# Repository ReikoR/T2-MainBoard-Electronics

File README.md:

T2-MainBoard-Electronics
========================

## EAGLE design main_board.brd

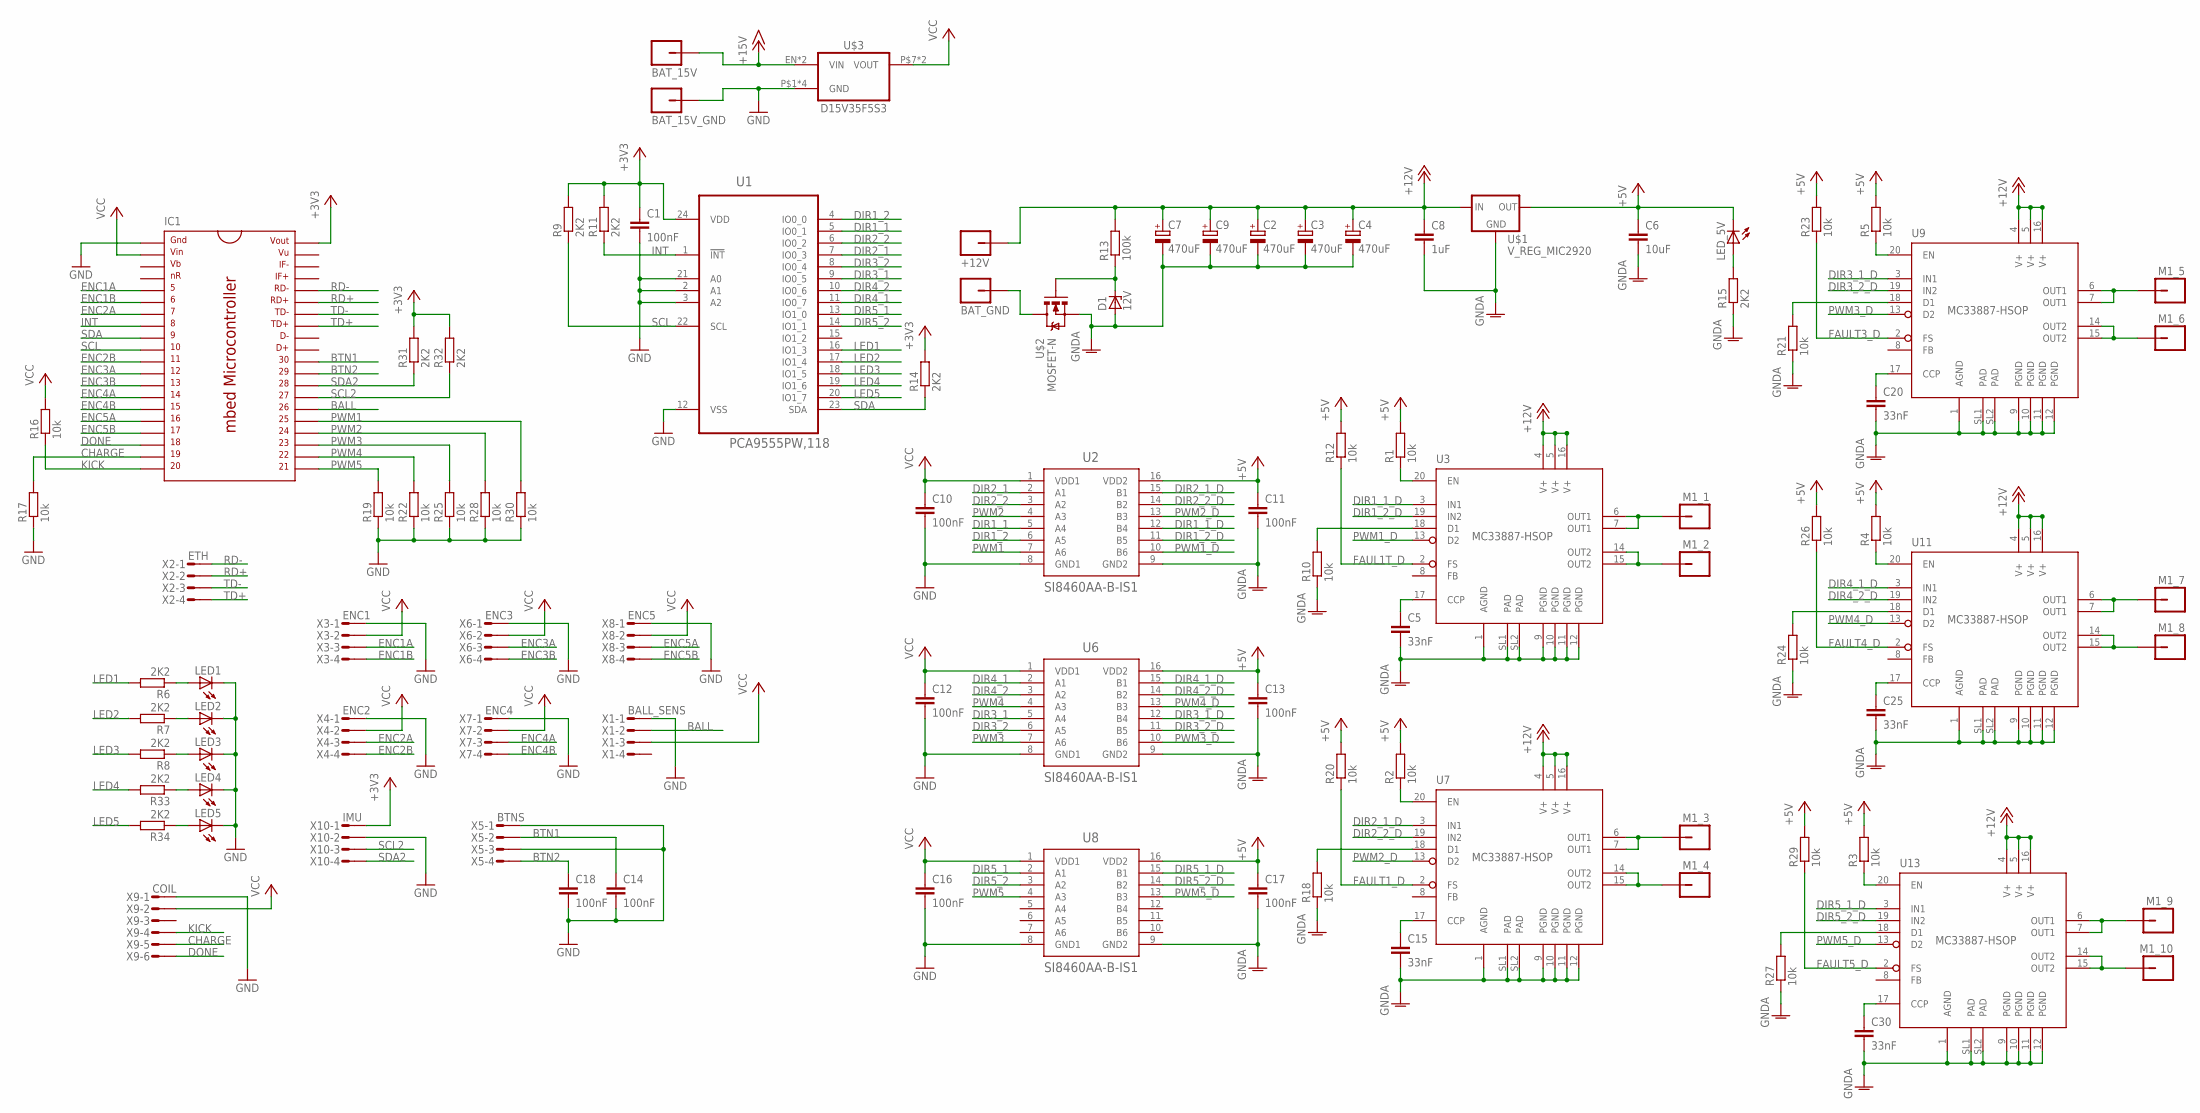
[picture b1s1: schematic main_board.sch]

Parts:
+12V: M01_PWR; PWR_HOLE
BAT_15V, BAT_15V_GND: M01_WIRE; WIRE_HOLE
BAT_GND: M01_PWR; PWR_HOLE
C1, C10, C11, C12, C13, C14, C16, C17, C18: 100nF; C0603K
C2, C3, C4, C7, C9: 470uF; E3,5-8
C5, C15, C20, C25, C30: 33nF; C0603K
C6: 10uF; C1206K
C8: 1uF; C0603K
D1: 12V; SOD123
IC1: MBED_MICROCONTROLLER; DIL40_0.9
LED1, LED2, LED3, LED4, LED5: LEDCHIP-LED0603; CHIP-LED0603
LED_5V: LEDCHIP-LED0603; CHIP-LED0603
M1_1, M1_2, M1_3, M1_4, M1_5, M1_6, M1_7, M1_8, M1_9, M1_10: M01_WIRE; WIRE_HOLE
R1, R2, R3, R4, R5, R10, R12, R16, R17, R18, R19, R20, R21, R22, R23, R24, R25, R26, R27, R28, R29, R30: 10k; R0603
R6, R7, R8, R9, R11, R14, R15, R31, R32, R33, R34: 2K2; R0603
R13: 100k; R0603
U1: PCA9555PW,118; SOP65P640X110-24N
U2, U6, U8: SI8460AA-B-IS1; SOIC-16
U3, U7, U9, U11, U13: MC33887-HSOP; HSOP
U$1: V_REG_MIC2920; SOT223
U$2: MOSFET-N; TO127P600X120-5N
U$3: D15V35F5S3
X1: BALL_SENS; MICROMATCH-4
X2: ETH; MICROMATCH-4
X3: ENC1; MICROMATCH-4
X4: ENC2; MICROMATCH-4
X5: BTNS; MICROMATCH-4
X6: ENC3; MICROMATCH-4
X7: ENC4; MICROMATCH-4
X8: ENC5; MICROMATCH-4
X9: COIL; MICROMATCH-6
X10: IMU; MICROMATCH-4

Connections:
+3V3: C1.1, IC1.40, R9.2, R11.2, R14.2, R31.2, R32.2, U1.24 (VDD), X10.1
+5V: C6.1, C11.1, C13.1, C17.1, LED_5V.C, R1.2, R2.2, R3.2, R4.2, R5.2, R12.2, R20.2, R23.2, R26.2, R29.2, U2.16 (VDD2), U6.16 (VDD2), U8.16 (VDD2), U$1.3 (OUT)
+12V: +12V.P$1, C2.+, C3.+, C4.+, C7.+, C8.1, C9.+, R13.2, U3.4 (V+), U3.5 (V+), U3.16 (V+), U7.4 (V+), U7.5 (V+), U7.16 (V+), U9.4 (V+), U9.5 (V+), U9.16 (V+), U11.4 (V+), U11.5 (V+), U11.16 (V+), U13.4 (V+), U13.5 (V+), U13.16 (V+), U$1.1 (IN)
+15V: BAT_15V.P$1, U$3.EN (VIN), U$3.P$5 (VIN)
BALL: IC1.26, X1.2
BTN1: C14.1, IC1.30, X5.2
BTN2: C18.1, IC1.29, X5.4
CHARGE: IC1.19, R17.2, X9.5
DIR1_1: U1.5 (IO0_1), U2.5 (A4)
DIR1_1_D: U2.12 (B4), U3.3 (IN1)
DIR1_2: U1.4 (IO0_0), U2.6 (A5)
DIR1_2_D: U2.11 (B5), U3.19 (IN2)
DIR2_1: U1.7 (IO0_3), U2.2 (A1)
DIR2_1_D: U2.15 (B1), U7.3 (IN1)
DIR2_2: U1.6 (IO0_2), U2.3 (A2)
DIR2_2_D: U2.14 (B2), U7.19 (IN2)
DIR3_1: U1.9 (IO0_5), U6.5 (A4)
DIR3_1_D: U6.12 (B4), U9.3 (IN1)
DIR3_2: U1.8 (IO0_4), U6.6 (A5)
DIR3_2_D: U6.11 (B5), U9.19 (IN2)
DIR4_1: U1.11 (IO0_7), U6.2 (A1)
DIR4_1_D: U6.15 (B1), U11.3 (IN1)
DIR4_2: U1.10 (IO0_6), U6.3 (A2)
DIR4_2_D: U6.14 (B2), U11.19 (IN2)
DIR5_1: U1.13 (IO1_0), U8.2 (A1)
DIR5_1_D: U8.15 (B1), U13.3 (IN1)
DIR5_2: U1.14 (IO1_1), U8.3 (A2)
DIR5_2_D: U8.14 (B2), U13.19 (IN2)
DONE: IC1.18, X9.6
ENC1A: IC1.5, X3.3
ENC1B: IC1.6, X3.4
ENC2A: IC1.7, X4.3
ENC2B: IC1.11, X4.4
ENC3A: IC1.12, X6.3
ENC3B: IC1.13, X6.4
ENC4A: IC1.14, X7.3
ENC4B: IC1.15, X7.4
ENC5A: IC1.16, X8.3
ENC5B: IC1.17, X8.4
FAUL1T_D: R12.1, U3.2 (FS)
FAULT1_D: R20.1, U7.2 (FS)
FAULT3_D: R23.1, U9.2 (FS)
FAULT4_D: R26.1, U11.2 (FS)
FAULT5_D: R29.1, U13.2 (FS)
GND: BAT_15V_GND.P$1, C1.2, C10.2, C12.2, C14.2, C16.2, C18.2, IC1.1, LED1.C, LED2.C, LED3.C, LED4.C, LED5.C, R17.1, R19.1, R22.1, R25.1, R28.1, R30.1, U1.2 (A1), U1.3 (A2), U1.12 (VSS), U1.21 (A0), U2.8 (GND1), U6.8 (GND1), U8.8 (GND1), U$3.P$1 (GND), U$3.P$2 (GND), U$3.P$3 (GND), U$3.P$4 (GND), X1.1, X3.1, X4.1, X5.1, X5.3, X6.1, X7.1, X8.1, X9.1, X10.2
GNDA: C2.-, C3.-, C4.-, C5.2, C6.2, C7.-, C8.2, C9.-, C11.2, C13.2, C15.2, C17.2, C20.2, C25.2, C30.2, D1.A, R10.1, R15.1, R18.1, R21.1, R24.1, R27.1, U2.9 (GND2), U3.1 (AGND), U3.9 (PGND), U3.10 (PGND), U3.11 (PGND), U3.12 (PGND), U3.SL1 (PAD), U3.SL2 (PAD), U6.9 (GND2), U7.1 (AGND), U7.9 (PGND), U7.10 (PGND), U7.11 (PGND), U7.12 (PGND), U7.SL1 (PAD), U7.SL2 (PAD), U8.9 (GND2), U9.1 (AGND), U9.9 (PGND), U9.10 (PGND), U9.11 (PGND), U9.12 (PGND), U9.SL1 (PAD), U9.SL2 (PAD), U11.1 (AGND), U11.9 (PGND), U11.10 (PGND), U11.11 (PGND), U11.12 (PGND), U11.SL1 (PAD), U11.SL2 (PAD), U13.1 (AGND), U13.9 (PGND), U13.10 (PGND), U13.11 (PGND), U13.12 (PGND), U13.SL1 (PAD), U13.SL2 (PAD), U$1.2 (GND), U$1.4 (GND), U$2.1 (S), U$2.2 (S), U$2.3 (S)
INT: IC1.8, R11.1, U1.1 (!INT)
KICK: IC1.20, R16.1, X9.4
LED1: R6.2, U1.16 (IO1_3)
LED2: R7.2, U1.17 (IO1_4)
LED3: R8.2, U1.18 (IO1_5)
LED4: R33.2, U1.19 (IO1_6)
LED5: R34.2, U1.20 (IO1_7)
unnamed: R1.1, U3.20 (EN)
unnamed: R2.1, U7.20 (EN)
unnamed: R3.1, U13.20 (EN)
unnamed: R4.1, U11.20 (EN)
unnamed: R5.1, U9.20 (EN)
unnamed: LED1.A, R6.1
unnamed: LED2.A, R7.1
unnamed: LED3.A, R8.1
unnamed: LED_5V.A, R15.2
unnamed: LED4.A, R33.1
unnamed: LED5.A, R34.1
unnamed: C5.1, U3.17 (CCP)
unnamed: R10.2, U3.18 (D1)
unnamed: D1.C, R13.1, U$2.4 (G)
unnamed: BAT_GND.P$1, U$2.5 (D)
unnamed: M1_1.P$1, U3.6 (OUT1), U3.7 (OUT1)
unnamed: M1_2.P$1, U3.14 (OUT2), U3.15 (OUT2)
unnamed: C15.1, U7.17 (CCP)
unnamed: R18.2, U7.18 (D1)
unnamed: M1_3.P$1, U7.6 (OUT1), U7.7 (OUT1)
unnamed: M1_4.P$1, U7.14 (OUT2), U7.15 (OUT2)
unnamed: C20.1, U9.17 (CCP)
unnamed: R21.2, U9.18 (D1)
unnamed: M1_5.P$1, U9.6 (OUT1), U9.7 (OUT1)
unnamed: M1_6.P$1, U9.14 (OUT2), U9.15 (OUT2)
unnamed: C25.1, U11.17 (CCP)
unnamed: R24.2, U11.18 (D1)
unnamed: M1_7.P$1, U11.6 (OUT1), U11.7 (OUT1)
unnamed: M1_8.P$1, U11.14 (OUT2), U11.15 (OUT2)
unnamed: C30.1, U13.17 (CCP)
unnamed: R27.2, U13.18 (D1)
unnamed: M1_9.P$1, U13.6 (OUT1), U13.7 (OUT1)
unnamed: M1_10.P$1, U13.14 (OUT2), U13.15 (OUT2)
PWM1: IC1.25, R30.2, U2.7 (A6)
PWM1_D: U2.10 (B6), U3.13 (D2)
PWM2: IC1.24, R28.2, U2.4 (A3)
PWM2_D: U2.13 (B3), U7.13 (D2)
PWM3: IC1.23, R25.2, U6.7 (A6)
PWM3_D: U6.10 (B6), U9.13 (D2)
PWM4: IC1.22, R22.2, U6.4 (A3)
PWM4_D: U6.13 (B3), U11.13 (D2)
PWM5: IC1.21, R19.2, U8.4 (A3)
PWM5_D: U8.13 (B3), U13.13 (D2)
RD+: IC1.35, X2.2
RD-: IC1.36, X2.1
SCL: IC1.10, R9.1, U1.22 (SCL)
SCL2: IC1.27, R32.1, X10.3
SDA: IC1.9, R14.1, U1.23 (SDA)
SDA2: IC1.28, R31.1, X10.4
TD+: IC1.33, X2.4
TD-: IC1.34, X2.3
VCC: C10.1, C12.1, C16.1, IC1.2, R16.2, U2.1 (VDD1), U6.1 (VDD1), U8.1 (VDD1), U$3.P$7 (VOUT), U$3.P$8 (VOUT), X1.3, X3.2, X4.2, X6.2, X7.2, X8.2, X9.2

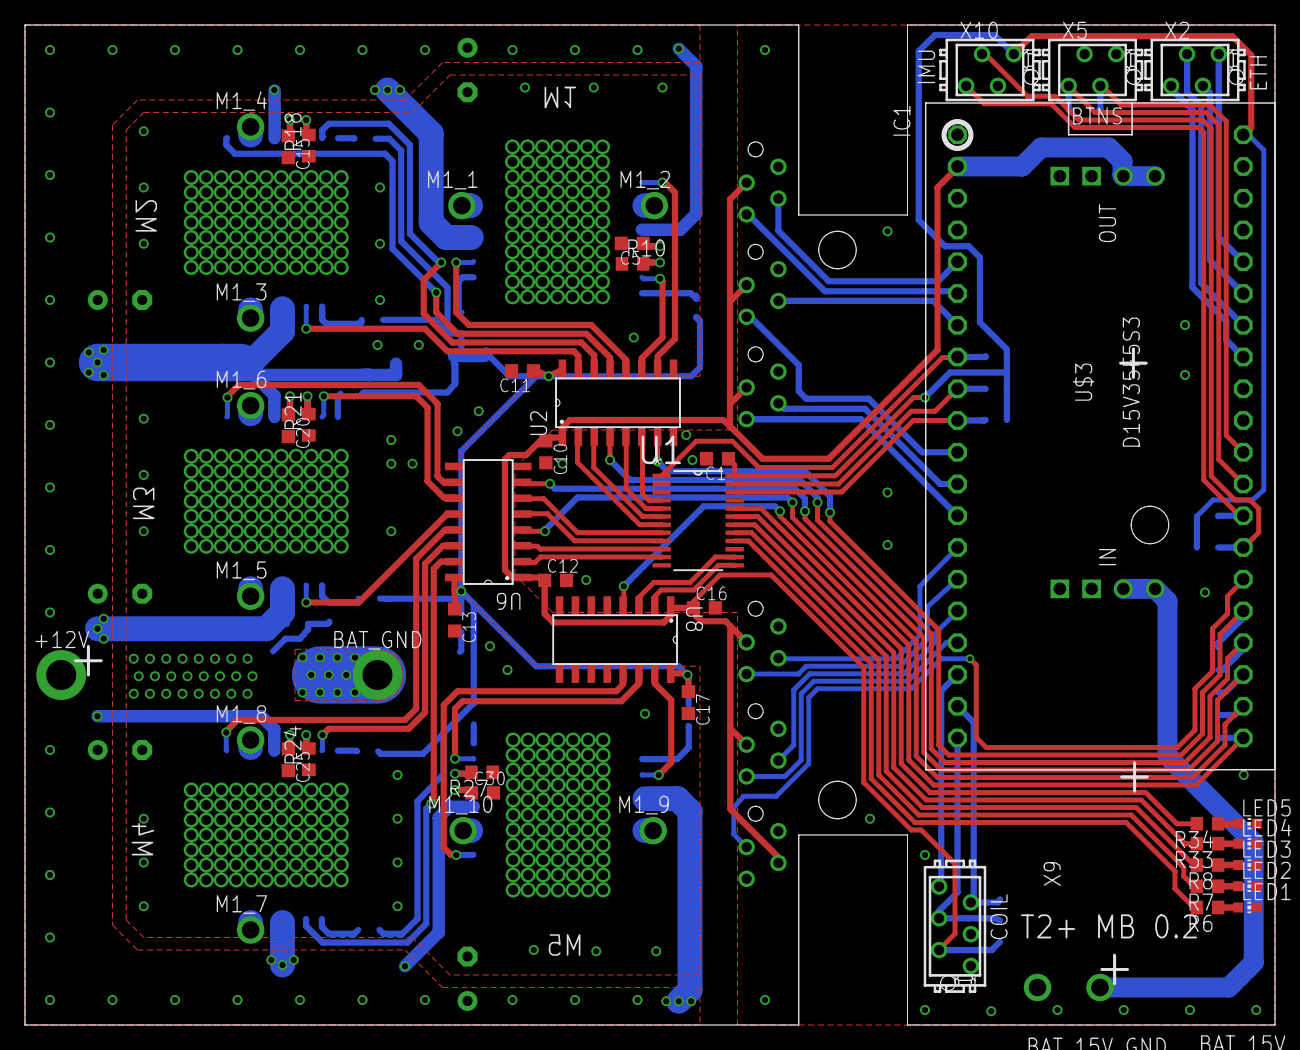
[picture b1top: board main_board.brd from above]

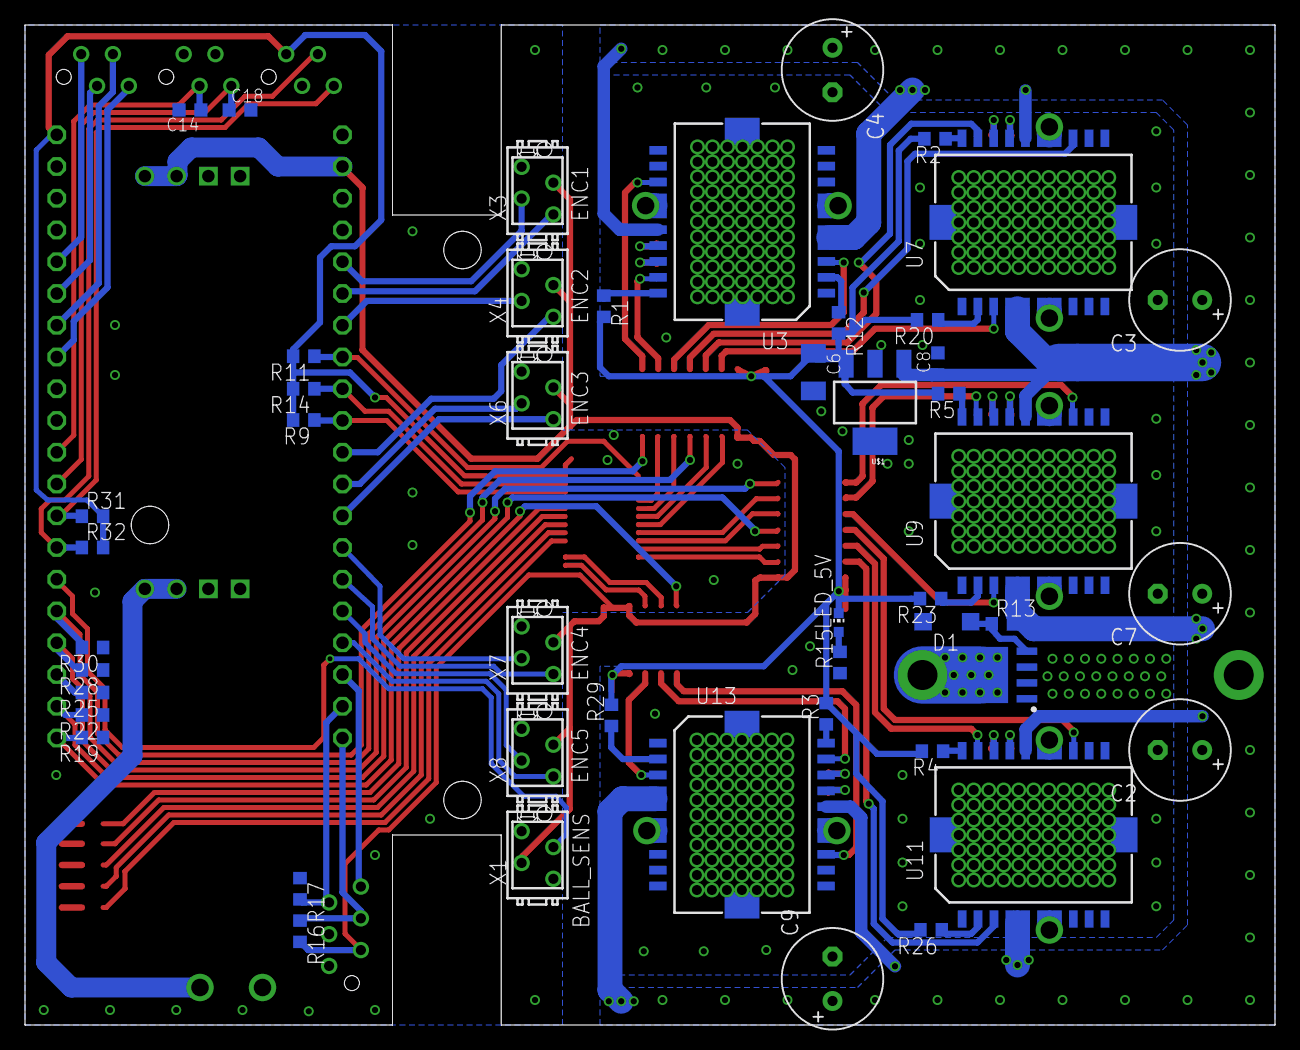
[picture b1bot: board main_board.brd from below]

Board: 2 copper layers, 100.0 x 80.0 mm, 99 parts (48 on the bottom side), 105 nets.

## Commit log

2013-07-14 Created schematic and board with main components
2013-08-03 Major changes, nearly ready for first prototype
2013-08-17 Improved board layout
2013-08-19 Added some labels and vias
2013-09-22 Added capacitor to buttons, switched IMU and buttons connector positions, moved voltage regulator to better position, connected IMU connector to second I2C pins added pull-down resistors to PWM pins,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
2013-09-24 Added two more LEDs to IO extender pins, connected buttons directly to mbed
2013-10-22 Connected ball detector directly to mbed
2013-10-22 Few small changes

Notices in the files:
parts and their libraries:
SparkFun-PowerIC: Licensing: CC v3.0 Share-Alike You are welcome to use this library for commercial purposes.
